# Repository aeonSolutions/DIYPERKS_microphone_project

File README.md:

[PCB-Prototyping-Catalogue](https://github.com/aeonSolutions/PCB-Prototyping-Catalogue)  >>  [Home-Automation](https://github.com/aeonSolutions/PCB-Prototyping-Catalogue/tree/main/Home-Automation)  >>  [Smart Home Appliances](https://github.com/aeonSolutions/PCB-Prototyping-Catalogue/tree/main/Home-Automation/Smart%20Home%20Appliances)  >>  [Living Room](https://github.com/aeonSolutions/PCB-Prototyping-Catalogue/tree/main/Home-Automation/Smart%20Home%20Appliances/Living%20Room) 

# DIYPERKS DIY "Building a quality USB-C microphone" 

This is the Gerber & KiCad files for the Youtuber DIY PERKS video "Building a quality USB-C microphone"
You can view the DIY build here : https://www.youtube.com/watch?v=LoQu3XXIayc&t=1s

If you prefer can read this project on Autodesk's Instructables.com website, [here](https://www.instructables.com/DIYPERKS-DIY-Building-a-Quality-USB-C-Microphone/).

*Don't forget to LIKE , SHARE and subscribe the free whatsApp group* and if you liked this PCB consider buying me a cup of coffee. Links below.

You have 2 options:

Download this repository for the KiCad Files pr, download the Gerber files in the release section of this repository

### alternatively if you do not want to build a PCB by yourself, and like to buy one mail me at mtpsilva@gmail.com. The price will be around 20eur plus postage fees.
(I will also deliver the assembled PCB with all the components in place at an aditonal cost).

<br>

## Compatibility

<p align="center">

</p>

<br>

## Q&A WhatsApp Group
If you have any Questions or simply  like this kind of projects and want to stay updated with the latest research ideas and prototypes during the day and week, join the WhatsApp Group
[LDAD Lab & Prototyping](https://chat.whatsapp.com/FkNC7u83kuy2QRA5sqjBVg)

________________________________________________________________________________________________________________

### Below was partly copied from the video description on YouTube

#### PCB Parts list:

Microphone capsule: https://www.jlielectronics.com/microphone-capsules/jli-2555bxz3-gp/

Shipping to the EU is expensive, so I'm working on a group buy. Check back in a few weeks' time!

#### Transistor 

US: https://ebay.us/3m3kyV

UK: https://ebay.us/KYIbZB

China (AliExpress.com): https://s.click.aliexpress.com/e/_AZ1Cqd

####  THAT1512 

US: https://www.newark.com/search?st=that1512

UK: https://ebay.us/wvJUzJ

China (AliExpress.com): https://s.click.aliexpress.com/e/_9ufNNf

####  USB Audio interface

https://amzn.to/3k43hy7

https://s.click.aliexpress.com/e/_9R7Nkz

####  USB C breakout board

https://amzn.to/3EJa0Fs

https://s.click.aliexpress.com/e/_9jZgBr

#### Capacitors
C1, C2, C5 : https://s.click.aliexpress.com/e/_A0ztiz

C3, C4, C6, C7 : https://s.click.aliexpress.com/e/_AmoZrX

#### JST Connectors
2 pins : https://s.click.aliexpress.com/e/_AYOqTb

3 pins : https://s.click.aliexpress.com/e/_AYOqTb

#### Resistors
100R : https://s.click.aliexpress.com/e/_9Ar1gt

2k2R : https://s.click.aliexpress.com/e/_9Ar1gt

3k9R : https://s.click.aliexpress.com/e/_9Ar1gt

_________________________________________________________________________________________________________________________________

####  7mm brass tube

Amazon: https://amzn.to/3BFJ086

eBay: https://ebay.us/pZfjF7

China (AliExpress): https://s.click.aliexpress.com/e/_A1CrZJ

####  6mm brass rod

Amazon: https://amzn.to/3mEPDDr

eBay: https://ebay.us/LAdYfs

China (AliExpress): https://s.click.aliexpress.com/e/_A1CrZJ

####  3mm brass rods

Amazon: https://amzn.to/3bCP9Hu

eBay: https://ebay.us/32ofym

China (AliExpress): https://s.click.aliexpress.com/e/_A1CrZJ

####  72mm 1.5mm nitrile o-rings

Amazon: https://amzn.to/3q6fvtV

eBay: https://ebay.us/y37Lmz

####  Brass mesh:

https://amzn.to/3mG1Zet

####  1- 5v +- isolator
 
https://ebay.us/YIIMNe

Cheaper version (but should work): https://ebay.us/Bwgafo or https://uk.rs-online.com/web/p/isolated-dc-dc-converters/2233683

For the resistors, capacitors, wire, stripboard etc:

https://www.bitsbox.co.uk/

https://s.click.aliexpress.com/e/_AV0cWz

USB C info: https://www.youtube.com/watch?v=V-vFtiDYiIw

#### If you like to  email DIY PERKS : DIYPerks@gmail.com
______________________________________________________________________________________________________________________________

### License
2022 Creative Commons Attribution-NonCommercial-ShareAlike 4.0 International

https://creativecommons.org/licenses/by-nc-sa/4.0/

### Own a copy of this work
if you like to own a copy of this work, you can buy it as a NFT or Ethereum. Contact me for more details at mtpsilva@gmail.com

=====================================================================================
### Share this PCB board files

### Be supportive of my dedication and work towards technology education and buy me a coffee

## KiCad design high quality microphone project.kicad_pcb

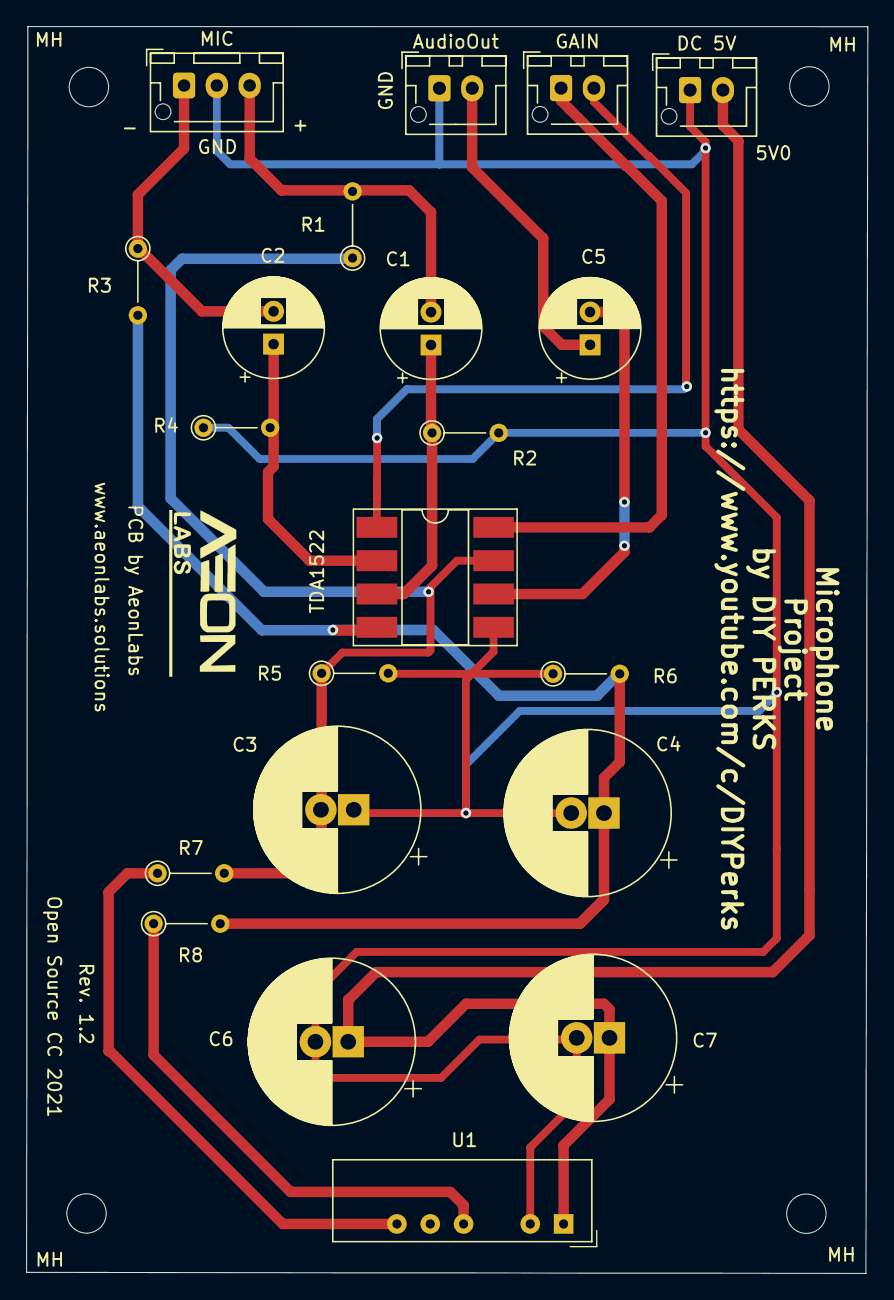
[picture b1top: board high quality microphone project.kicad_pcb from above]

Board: 2 copper layers, 64.1 x 95.0 mm, 25 parts (0 on the bottom side), 14 nets.

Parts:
AudioOut: Audio Out; JST_XH_B2B-XH-AM_1x02_P2.50mm_Vertical
C1, C2, C5: 22pF; CP_Radial_D7.5mm_P2.50mm
C3, C4, C6, C7: 2200pF; CP_Radial_D12.5mm_P2.50mm
DC 5V: USB 5V; JST_XH_B2B-XH-AM_1x02_P2.50mm_Vertical
GAIN: GAIN; JST_XH_B2B-XH-AM_1x02_P2.50mm_Vertical
MH: MountingHole_3mm
MH#2, MH#3, MH#4: MountingHole_3mm
MIC: MIC; JST_XH_B3B-XH-AM_1x03_P2.50mm_Vertical
R1, R3, R5, R6: 2k2; R_Axial_DIN0204_L3.6mm_D1.6mm_P5.08mm_Vertical
R2, R4: 3k9; R_Axial_DIN0204_L3.6mm_D1.6mm_P5.08mm_Vertical
R7, R8: 100; R_Axial_DIN0204_L3.6mm_D1.6mm_P5.08mm_Vertical
TDA1522: TDA1522; DIP-8_W8.89mm_SMDSocket_LongPads
U1: NMA0515SC; Converter_DCDC_muRata_NMAxxxxSC_THT

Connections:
unnamed: AudioOut.1, C3.1, C4.2, C6.2, C7.2, DC 5V.1, MIC.2, R2.2, R4.1, R5.2, R6.1, TDA1522.5, U1.2
unnamed: AudioOut.2, C5.1
unnamed: C1.1, R2.1, TDA1522.3
unnamed: C1.2, MIC.3, R1.2
unnamed: C2.1, R4.2, TDA1522.2
unnamed: C2.2, MIC.1, R3.1
unnamed: C3.2, R1.1, R5.1, R7.2, TDA1522.7
unnamed: C4.1, R3.2, R6.2, R8.2, TDA1522.4
unnamed: C5.2, TDA1522.6
unnamed: C6.1, C7.1, DC 5V.2, U1.1
unnamed: GAIN.1, TDA1522.8
unnamed: GAIN.2, TDA1522.1
unnamed: R7.1, U1.6
unnamed: R8.1, U1.4

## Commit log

2021-11-07 pcb revision 1.1
2021-11-08 Add files via upload
    corrected a DRC error in a track.
    Added Pinout text to the JST plugs
2021-11-08 Update README.md
    added pcb components. Namely capacitors, resistors, JST connectots
